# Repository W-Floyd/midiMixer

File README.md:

# midiMixer

A project to create some simple, low cost MIDI mixers, so I can easily control instruments in my DAW.

This is also going to be a learning experience for me.

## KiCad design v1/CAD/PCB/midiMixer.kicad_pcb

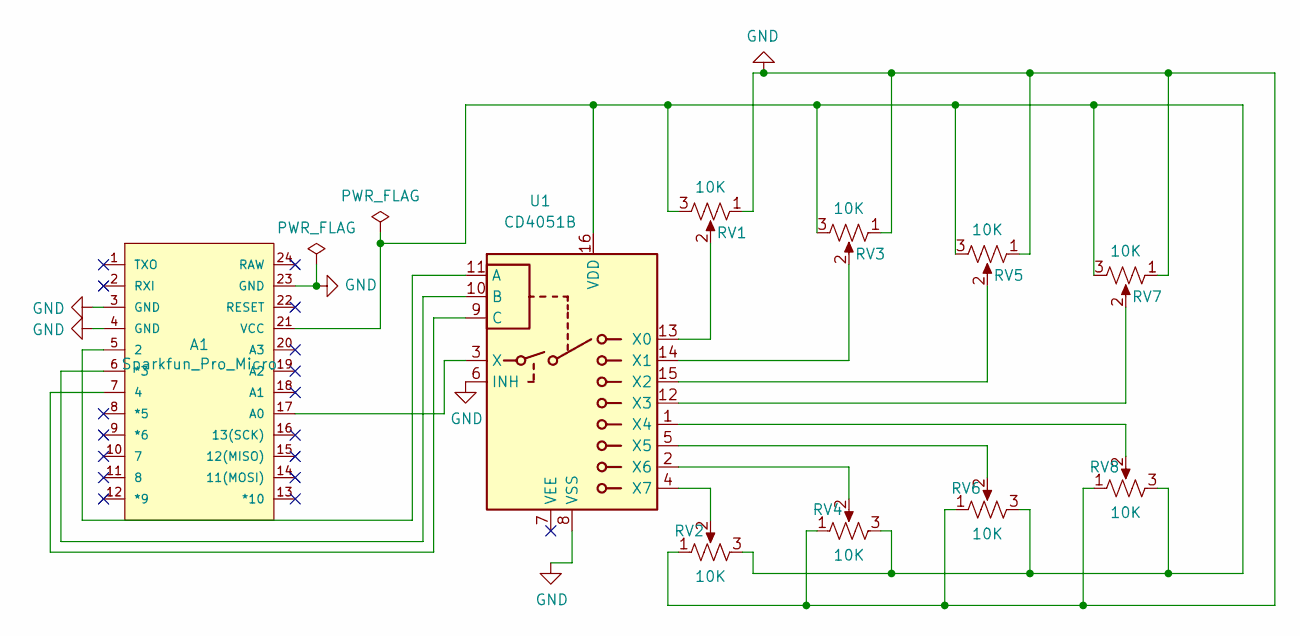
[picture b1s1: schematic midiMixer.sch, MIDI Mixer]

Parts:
A1: Sparkfun_Pro_Micro; SPARKFUN_PRO_MICRO
RV1, RV2, RV3, RV4, RV5, RV6, RV7, RV8: 10K; Potentiometer_Alpha_RD901F-40-00D_Single_Vertical_CircularH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
U1: CD4051B; DIP-16_W7.62mm

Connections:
GND: A1.3 (GND), A1.4 (GND), A1.23 (GND), RV1.1, RV2.1, RV3.1, RV4.1, RV5.1, RV6.1, RV7.1, RV8.1, U1.6 (INH), U1.8 (VSS)
unnamed: A1.5 (2), U1.11 (A)
unnamed: A1.6 (*3), U1.10 (B)
unnamed: A1.7 (4), U1.9 (C)
unnamed: A1.17 (A0), U1.3 (X)
unnamed: A1.21 (VCC), RV1.3, RV2.3, RV3.3, RV4.3, RV5.3, RV6.3, RV7.3, RV8.3, U1.16 (VDD)
unnamed: RV1.2, U1.13 (X0)
unnamed: RV2.2, U1.4 (X7)
unnamed: RV3.2, U1.14 (X1)
unnamed: RV4.2, U1.2 (X6)
unnamed: RV5.2, U1.15 (X2)
unnamed: RV6.2, U1.5 (X5)
unnamed: RV7.2, U1.12 (X3)
unnamed: RV8.2, U1.1 (X4)

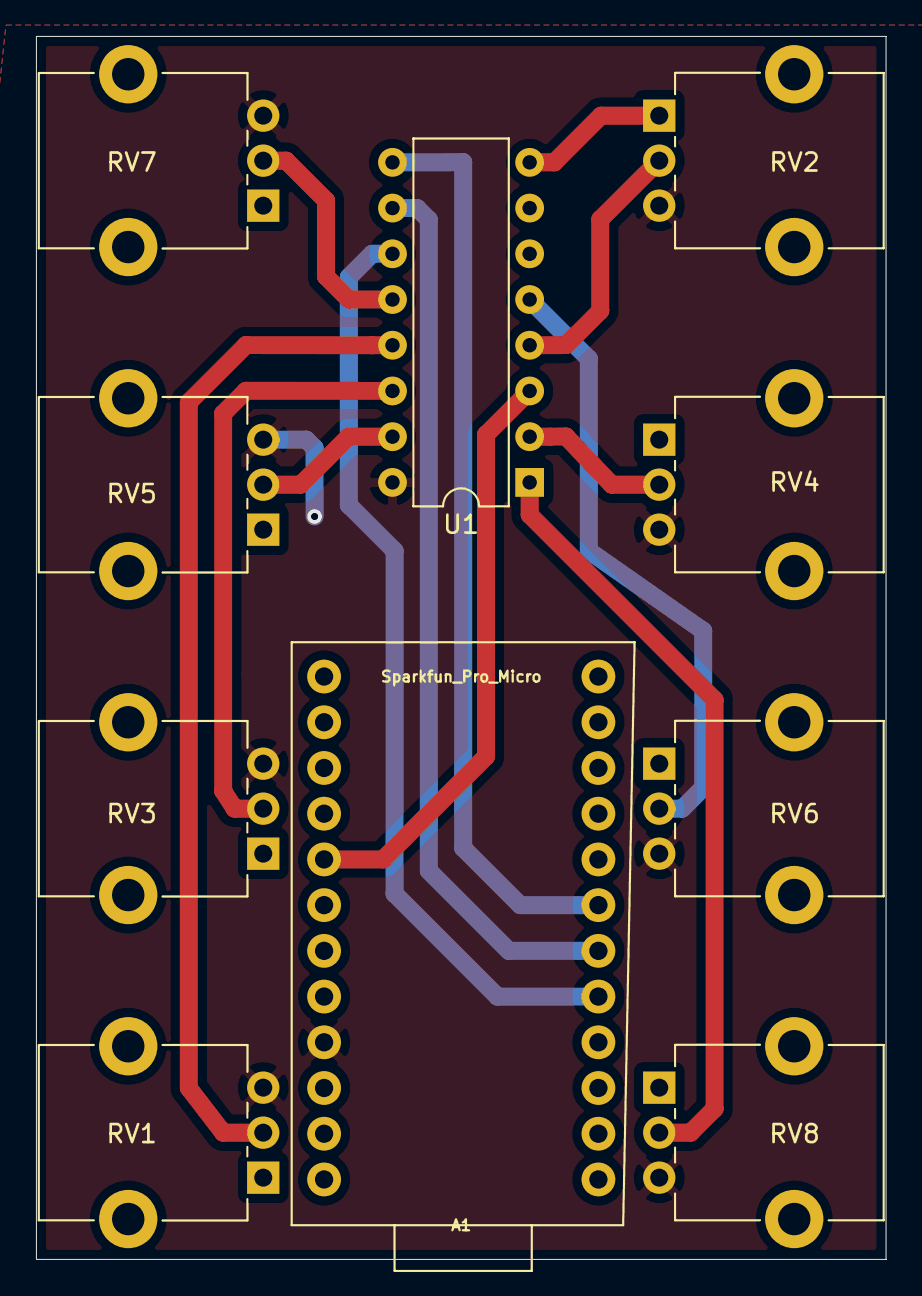
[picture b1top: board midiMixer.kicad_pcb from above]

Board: 2 copper layers, 47.2 x 67.9 mm, 10 parts (0 on the bottom side), 14 nets.

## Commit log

2020-05-06 midiMixer: Add code for midiMixer v1.
2020-05-06 v1: move out of subfolder
2020-05-06 v1/code: Final move...
2020-05-06 gitattributes: Add git lfs for binary files like CAD and Gerber ZIP.
2020-05-06 v1/CAD/3D: Add some parts I printed.
2020-05-06 v1/CAD/PCB: Add KiCAD files and Gerber ZIP.
2020-05-06 README / v1/README : Add READMEs for project as a whole, and for v1.
2020-05-07 v1/README_v1: Link to blog post.

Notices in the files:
v1/CAD/PCB/midiMixer.kicad_pcb:
©William Floyd 2020
